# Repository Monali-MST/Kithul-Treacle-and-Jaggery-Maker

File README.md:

# Kithul-Treacle-and-Jaggery-Maker
1st year hardware project

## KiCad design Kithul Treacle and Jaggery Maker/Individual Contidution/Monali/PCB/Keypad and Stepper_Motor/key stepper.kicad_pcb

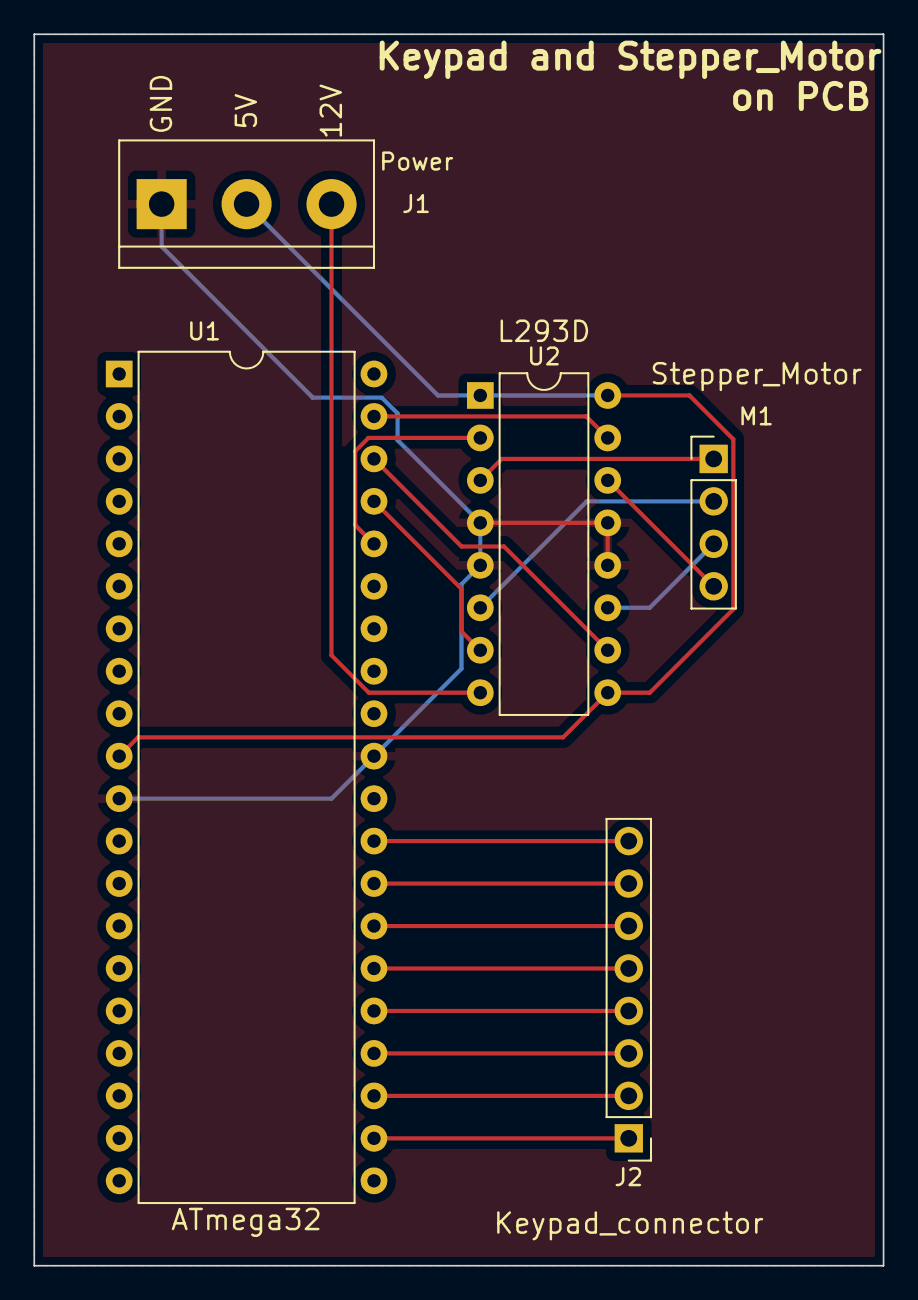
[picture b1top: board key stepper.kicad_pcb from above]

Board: 2 copper layers, 50.8 x 73.7 mm, 5 parts (0 on the bottom side), 19 nets.

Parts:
J1: Power; TerminalBlock_bornier-3_P5.08mm
J2: Keypad_connector; PinHeader_1x08_P2.54mm_Vertical
M1: Stepper_Motor; PinHeader_1x04_P2.54mm_Vertical
U1: ATmega32; DIP-40_W15.24mm
U2: L293D; DIP-16_W7.62mm

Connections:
GND: J1.1, U1.11 (GND), U1.31 (GND), U2.4 (GND), U2.5 (GND), U2.12 (GND), U2.13 (GND)
unnamed: J1.2, U1.10 (VCC), U2.1 (EN1,2), U2.9 (EN3,4), U2.16 (VCC1)
unnamed: J1.3, U2.8 (VCC2)
unnamed: J2.1, U1.22 (PC0)
unnamed: J2.2, U1.23 (PC1)
unnamed: J2.3, U1.24 (PC2)
unnamed: J2.4, U1.25 (PC3)
unnamed: J2.5, U1.26 (PC4)
unnamed: J2.6, U1.27 (PC5)
unnamed: J2.7, U1.28 (PC6)
unnamed: J2.8, U1.29 (PC7)
unnamed: M1.1, U2.3 (1Y)
unnamed: M1.2 (-), U2.6 (2Y)
unnamed: M1.3, U2.11 (3Y)
unnamed: M1.4, U2.14 (4Y)
unnamed: U1.36 (PA4), U2.2 (1A)
unnamed: U1.37 (PA3), U2.7 (2A)
unnamed: U1.38 (PA2), U2.10 (3A)
unnamed: U1.39 (PA1), U2.15 (4A)

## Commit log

2022-09-10 deleted report 2.1mb
2022-09-10 add final report
2022-09-19 add individual part
2022-09-19 ppt and word individul
